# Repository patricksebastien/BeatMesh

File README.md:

# BeatMesh

A module to synchronize via Ableton Link, MIDI, or CV clock. 

Built with PlatformIO and the ESP-IDF framework (espressif32), BeatMesh acts as a hub to keep your hardware and software locked in time.

## 🚀 Features

- **10x MIDI Out ports**
- **Flexible Routing:** Send raw MIDI to all 10 outputs OR filter to keep only the MIDI clock.
- **CV Integration:** CV clock and reset outputs.
- **Ableton Link:** Synchronize seamlessly over WiFi.
- **Ignore Stop:** Jam-proof mode. Stop messages from Link peers, MIDI in or CV in are refused; only BeatMesh itself can stop the clock.
- **MIDI Metronome:** Clock-synced click on the MIDI outputs (note 72 on beat 1, 64 on beats 2-4, channel 1 or 10).
- **Tuner:** One long open-string note on MIDI channel 1, note on at the downbeat of every bar and retriggered at the next one, for tuning by ear. One button cycles through the six guitar strings (E2 A2 D3 G3 B3 E4).
- **Random MIDI (debug mode):** Random pentatonic notes on channels 1-6, random-walk CCs, and a simple four-on-the-floor drum pattern on channel 10, all locked to the clock.
- **OTA Firmware Updates:** Upload new firmware (`.bin`) directly from the web portal, no cable needed.
- **Easy Soldering:** All through-hole components (except USB-C, see below*), beginner-friendly assembly.
- **Easy to Print:** Two-piece 3D-printed case (top and bottom STL), no supports needed, held together with M3 screws.

---

## 🎛️ Custom PCB (KiCad)

The repository includes a production-ready printed circuit board designed in **KiCad 10**. You can find the source files (`.kicad_sch` and `.kicad_pcb`) in the `board/` directory.

<!-- V1 PCB errata (fixed on V2 boards):
> ⚠️ **V1 PCB Errata:** The 2-pin power connector near the USB-C port has its silkscreen polarity printed incorrectly. The actual pinout is **GND, VCC** (not VCC, GND as silkscreened). Wire accordingly to avoid damage.
-->

### Power & USB-C Assembly Notes*

The board only draws 5V power from USB-C; no data lines are used. Two shortcuts make assembly easier:

- **\*Skip the USB-C connector if you are new to soldering.** It is the only surface-mount part on the board; its pins are fine-pitch and tricky to solder by hand. Instead, cut an old USB cable, and solder its **VCC (red)** and **GND (black)** wires directly to the 2-pin power connector pads next to the USB-C footprint. Mind the polarity marked on the silkscreen.
- **The 5.1kΩ resistors (R2, R3) are only needed for USB-C to USB-C.** They are the CC pull-downs that tell a USB-C power adapter or USB-C host to turn on 5V. If you power the board with a **USB-A to USB-C** cable (phone charger, computer port, power bank), 5V is always present on VBUS and R2/R3 can be left unpopulated. In that case only the **VBUS and GND** pins of the USB-C connector need to be soldered.

### Hardware Design Highlights:
- **Form Factor:** 100mm x 100mm, 2-layer board (optimized for low-cost fabrication).
- **MIDI Input:** Fully opto-isolated using a **6N138** optocoupler. The circuit is properly level-shifted to send safe 3.3V logic to the ESP32, while powering the optocoupler with 5V for fast, reliable data transmission.
- **10x MIDI Outputs:** Buffered (using 2N3904 NPN transistors) and split to drive up to 10 distinct devices simultaneously without signal degradation. Designed with space-saving 3.5mm TRS jacks (SJ1-3515N).
- **CV / Sync Out:** Capable of sending analog clock, reset, and play/stop signals to Eurorack/modular gear. Includes **BAT41** Schottky diodes for signal protection.
- **CYD Integration:** Designed to interface cleanly with the Cheap Yellow Display (ESP32-2432S028R) ecosystem via standard 2.54mm pin headers.
- **Power Delivery:** Robust decoupling with 100nF ceramics and 47µF (25V) electrolytics to keep clock and CV paths stable and noise-free.

---

## 🖨️ 3D Printed Case

The case is two pieces, in the `3dprint/` folder:

- `3dprint/BeatMeshV2 - TOP.stl`
- `3dprint/BeatMeshV2 - BOTTOM.stl`

Both print flat on the bed with no supports. Any PLA or PETG works.

Hardware:

- **4x M3 x 30 mm** screws: hold the top and bottom pieces together, screwing straight through both boards.
- **4x M3 x 12 mm** screws with nuts: mount the CYD to the top piece.

---

## 🔊 Optional Metronome (Speaker)

The firmware has a built-in metronome (1200 Hz click on beat 1, 800 Hz on beats 2-4) that plays through the CYD's onboard audio amplifier on GPIO 26. It is **disabled by default** because most builds have no speaker, and the METRONOME button is hidden from the TFT and the web UI.

To use it:

1. Wire the CYD speaker connector to the **SPEAKER IN** header on the BeatMesh board.
2. Connect a small speaker (8 Ω, 0.5-1 W) to the **SPEAKER OUT** header on the BeatMesh board.
3. In `src/main.cpp`, change `#define BEATMESH_METRONOME 0` to `1`.
4. Recompile and flash (`pio run -t upload`, or upload the new `.bin` from the web portal). The metronome code is compiled out, so a rebuild is required; toggling it is not a runtime setting.

The METRONOME button then appears on the main screen (row 2, left of PPQN) and on the web page.

---

## 💻 Installation & Dependencies

> Built with PlatformIO platform `espressif32@6.12.0`, framework `espidf` (ESP-IDF v5.5.0).

External components live under `components/` as git submodules pinned to the versions used in this project:

| Submodule | Upstream | Pinned at |
|---|---|---|
| `components/asio/asio` | [chriskohlhoff/asio](https://github.com/chriskohlhoff/asio) | `asio-1-32-0` |
| `components/esp_abl_link` | [docwilco/esp_abl_link](https://github.com/docwilco/esp_abl_link) | `v3.1.5-1` |
| `components/esp_abl_link/vendor/ableton-link` | [Ableton/link](https://github.com/Ableton/link) | `Link-3.1.5` |
| `components/LovyanGFX` | [lovyan03/LovyanGFX](https://github.com/lovyan03/LovyanGFX) | `1.2.19` |

### Cloning

```bash
git clone --recurse-submodules https://github.com/patricksebastien/BeatMesh.git
```

If you already cloned without `--recurse-submodules`:

```bash
git submodule update --init --recursive
```

> Use `git config --global url."https://github.com/".insteadOf git@github.com:` if you don't have ssh key configured.

### ASIO Patch (Required)
To prevent the ESP32 from rebooting during transient network errors (e.g., `send_to ENOMEM`), ASIO needs a small patch. Link recovers from packet loss gracefully, so we do not want `std::terminate` to abort the program.

Apply the patch shipped in this repo:

```bash
git -C components/asio/asio apply ../../../patches/asio-esp32-rethrow-fix.patch
```

---

## ⚙️ Configuration Files

### 1. `platformio.ini`
Add the following to your environment configuration to ensure correct serial speeds, flash sizing, the OTA partition table, and ASIO compatibility:

```ini
[env:esp32dev]
platform = espressif32@6.12.0
board = esp32dev
framework = espidf
monitor_speed = 115200
board_upload.flash_size = 4MB
board_build.partitions = ota_4mb.csv    ; two ~1.94MB OTA slots (web firmware update)

extra_scripts = pre:git_version.py      ; injects GIT_VERSION (short commit hash) into the build

build_flags =
    -fexceptions
    -D ASIO_STANDALONE
    -D ASIO_NO_TYPEID
```

### 2. `ota_4mb.csv` (Partition Table)
Create this file in the root directory. Link and LovyanGFX make the binary quite large, so the default partition table is too small. Two ~1.94 MB app slots give room for the OTA web update while still fitting the ~1.4 MB image.

```csv
# Name,   Type, SubType, Offset,   Size, Flags
nvs,      data, nvs,     0x9000,   0x4000,
otadata,  data, ota,     0xd000,   0x2000,
phy_init, data, phy,     0xf000,   0x1000,
ota_0,    app,  ota_0,   0x10000,  0x1F0000,
ota_1,    app,  ota_1,   0x200000, 0x1F0000,
```

Changing the partition table requires one flash over USB; OTA works from then on.

### 3. `sdkconfig.defaults`
Create this file in the root directory. The essential settings are below; the full file in the repo also tunes WiFi buffers, LWIP, UDP mailboxes and TCP timeouts for up to 10 Link peers plus the web portal.

```ini
# Flash Size & Speed (CYD has a 4MB Flash chip)
CONFIG_ESPTOOLPY_FLASHSIZE_4MB=y
CONFIG_ESPTOOLPY_FLASHFREQ_80M=y
CONFIG_ESPTOOLPY_FLASHMODE_QIO=y

# C++ Exceptions (Required for ASIO/Link)
CONFIG_COMPILER_CXX_EXCEPTIONS=y
CONFIG_COMPILER_CXX_RTTI=y

# Partition Table Layout (OTA, see ota_4mb.csv above)
CONFIG_PARTITION_TABLE_CUSTOM=y
CONFIG_PARTITION_TABLE_CUSTOM_FILENAME="ota_4mb.csv"
CONFIG_BOOTLOADER_APP_ROLLBACK_ENABLE=y

# CPU Frequency (Ensure Link timing on Core 1 and Display/WiFi on Core 0 run smoothly)
CONFIG_ESP_DEFAULT_CPU_FREQ_MHZ_240=y
CONFIG_ESP_DEFAULT_CPU_FREQ_MHZ=240

# Link tasks on Core 1 (WiFi stays on Core 0)
CONFIG_LINK_ESP_TASK_CORE_ID=1

# LWIP (Networking for Link - Multicast support is crucial)
CONFIG_LWIP_MAX_SOCKETS=32
CONFIG_LWIP_IGMP=y
CONFIG_LWIP_SO_REUSE=y

# Disable Bluetooth (WiFi only)
CONFIG_BT_ENABLED=n
```

### 4. `src/CMakeLists.txt`
Include the necessary libraries via `REQUIRES` so ESP-IDF links them properly:

```cmake
idf_component_register(SRCS "main.cpp"
                    INCLUDE_DIRS "."
                    REQUIRES LovyanGFX esp_http_server nvs_flash esp_wifi esp_event esp_abl_link app_update)
```

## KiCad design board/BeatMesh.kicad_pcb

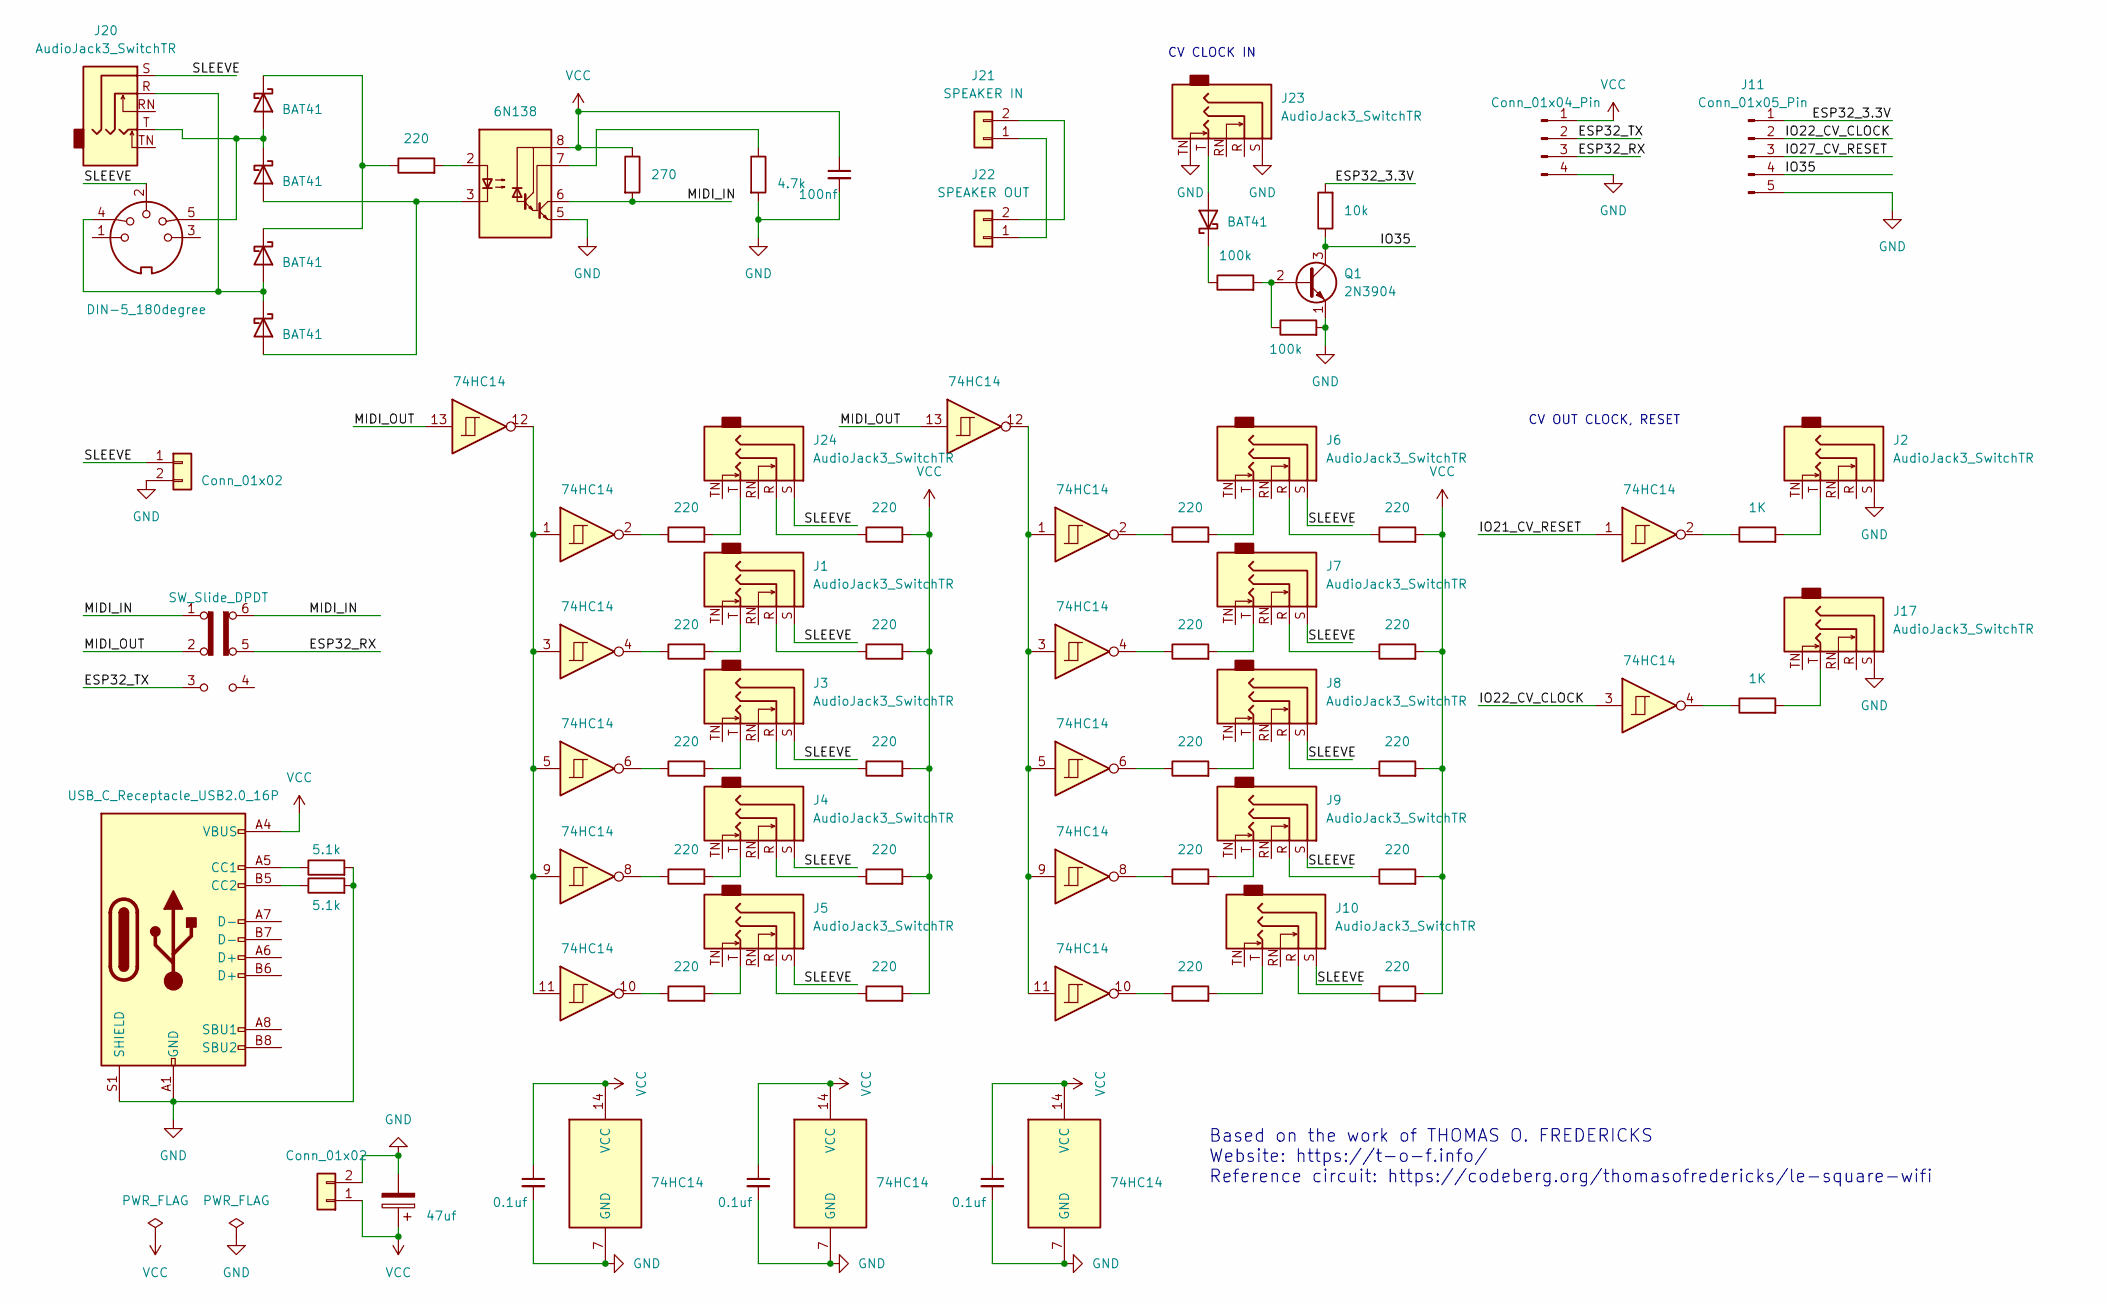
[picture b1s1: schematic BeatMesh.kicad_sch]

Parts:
C1, C2, C6: 0.1uf; C_Disc_D5.0mm_W2.5mm_P5.00mm
C3: 100nf; C_Disc_D5.0mm_W2.5mm_P5.00mm
C4: 47uf; CP_Radial_D5.0mm_P2.00mm
D1, D2, D3, D4, D6: BAT41; D_DO-35_SOD27_P7.62mm_Horizontal
J1, J2, J3, J4, J5, J6, J7, J8, J9, J10, J17, J20, J23, J24: AudioJack3_SwitchTR; Jack_3.5mm_CUI_SJ1-3515N_Horizontal
J11: Conn_01x05_Pin; PinHeader_1x05_P2.54mm_Vertical
J12: DIN-5_180degree; CUI_SDS-50J
J13: USB_C_Receptacle_USB2.0_16P; USB_C_Receptacle_HRO_TYPE-C-31-M-12
J14: Conn_01x04_Pin; PinHeader_1x04_P2.54mm_Vertical
J15, J16: Conn_01x02; PinHeader_1x02_P2.54mm_Vertical
J21: SPEAKER IN; PinHeader_1x02_P2.54mm_Vertical
J22: SPEAKER OUT; PinHeader_1x02_P2.54mm_Vertical
Q1: 2N3904; TO-92_Inline_Wide
R1, R6, R7, R8, R9, R10, R11, R12, R13, R14, R15, R16, R17, R18, R19, R20, R21, R22, R23, R24, R25: 220; R_Axial_DIN0204_L3.6mm_D1.6mm_P5.08mm_Horizontal
R2, R3: 5.1k; R_Axial_DIN0204_L3.6mm_D1.6mm_P5.08mm_Horizontal
R4: 270; R_Axial_DIN0204_L3.6mm_D1.6mm_P5.08mm_Horizontal
R5: 4.7k; R_Axial_DIN0204_L3.6mm_D1.6mm_P5.08mm_Horizontal
R26, R28: 1K; R_Axial_DIN0204_L3.6mm_D1.6mm_P5.08mm_Horizontal
R29, R31: 100k; R_Axial_DIN0204_L3.6mm_D1.6mm_P5.08mm_Horizontal
R30: 10k; R_Axial_DIN0204_L3.6mm_D1.6mm_P5.08mm_Horizontal
SW1: SW_Slide_DPDT; SW_E-Switch_EG2219_DPDT_Angled
U1, U2, U4: 74HC14; DIP-14_W7.62mm
U3: 6N138; DIP-8_W7.62mm

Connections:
/ESP32_3.3V: J11.1, R30.2
/ESP32_RX: J14.3, SW1.5 (B)
/ESP32_TX: J14.2, SW1.3 (C)
/IO21_CV_RESET: U4.1
/IO22_CV_CLOCK: J11.2, U4.3
/IO27_CV_RESET: J11.3
/IO35: J11.4, Q1.3 (C), R30.1
/MIDI_IN: R4.2, SW1.1 (A), SW1.6 (C), U3.6 (VO2)
/MIDI_OUT: SW1.2 (B), U1.13, U2.13
/SLEEVE: J1.S, J3.S, J4.S, J5.S, J6.S, J7.S, J8.S, J9.S, J10.S, J12.2, J15.1, J20.S, J24.S
GND: C1.2, C2.2, C3.2, C4.2, C6.2, J2.S, J11.5, J13.A1 (GND), J13.A12 (GND), J13.B1 (GND), J13.B12 (GND), J13.S1 (SHIELD), J14.4, J15.2, J16.2, J17.S, J23.S, J23.TN, Q1.1 (E), R2.2, R3.2, R5.2, R31.2, U1.7 (GND), U2.7 (GND), U3.5 (GND), U4.7 (GND)
unnamed: D1.2 (A), D2.1 (K), J12.5, J20.T
unnamed: D1.1 (K), D3.1 (K), R1.1
unnamed: D2.2 (A), D4.2 (A), U3.3 (C2)
unnamed: D3.2 (A), D4.1 (K), J12.4, J20.R
unnamed: D6.2 (A), J23.T
unnamed: D6.1 (K), R29.1
unnamed: J1.R, R12.1
unnamed: J1.T, R7.2
unnamed: J2.T, R26.2
unnamed: J3.R, R13.1
unnamed: J3.T, R8.2
unnamed: J4.R, R14.1
unnamed: J4.T, R9.2
unnamed: J5.R, R15.1
unnamed: J5.T, R10.2
unnamed: J6.R, R21.1
unnamed: J6.T, R16.2
unnamed: J7.R, R22.1
unnamed: J7.T, R17.2
unnamed: J8.R, R23.1
unnamed: J8.T, R18.2
unnamed: J9.R, R24.1
unnamed: J9.T, R19.2
unnamed: J10.R, R25.1
unnamed: J10.T, R20.2
unnamed: J13.A5 (CC1), R2.1
unnamed: J13.B5 (CC2), R3.1
unnamed: J17.T, R28.2
unnamed: J21.1, J22.1
unnamed: J21.2, J22.2
unnamed: J24.R, R11.1
unnamed: J24.T, R6.2
unnamed: Q1.2 (B), R29.2, R31.1
unnamed: R6.1, U2.2
unnamed: R7.1, U2.4
unnamed: R8.1, U2.6
unnamed: R9.1, U2.8
unnamed: R10.1, U2.10
unnamed: R16.1, U1.2
unnamed: R17.1, U1.4
unnamed: R18.1, U1.6
unnamed: R19.1, U1.8
unnamed: R20.1, U1.10
unnamed: R26.1, U4.2
unnamed: R28.1, U4.4
unnamed: U1.1, U1.3, U1.5, U1.9, U1.11, U1.12
unnamed: U2.1, U2.3, U2.5, U2.9, U2.11, U2.12
unnamed: R1.2, U3.2 (C1)
unnamed: R5.1, U3.7 (VO1)
VCC: C1.1, C2.1, C3.1, C4.1, C6.1, J13.A4 (VBUS), J13.A9 (VBUS), J13.B4 (VBUS), J13.B9 (VBUS), J14.1, J16.1, R4.1, R11.2, R12.2, R13.2, R14.2, R15.2, R21.2, R22.2, R23.2, R24.2, R25.2, U1.14 (VCC), U2.14 (VCC), U3.8 (VCC), U4.14 (VCC)

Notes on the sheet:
Based on the work of THOMAS O. FREDERICKS Website: https://t-o-f.info/ Reference circuit: https://codeberg.org/thomasofredericks/le-square-wifi
CV CLOCK IN
CV OUT CLOCK, RESET

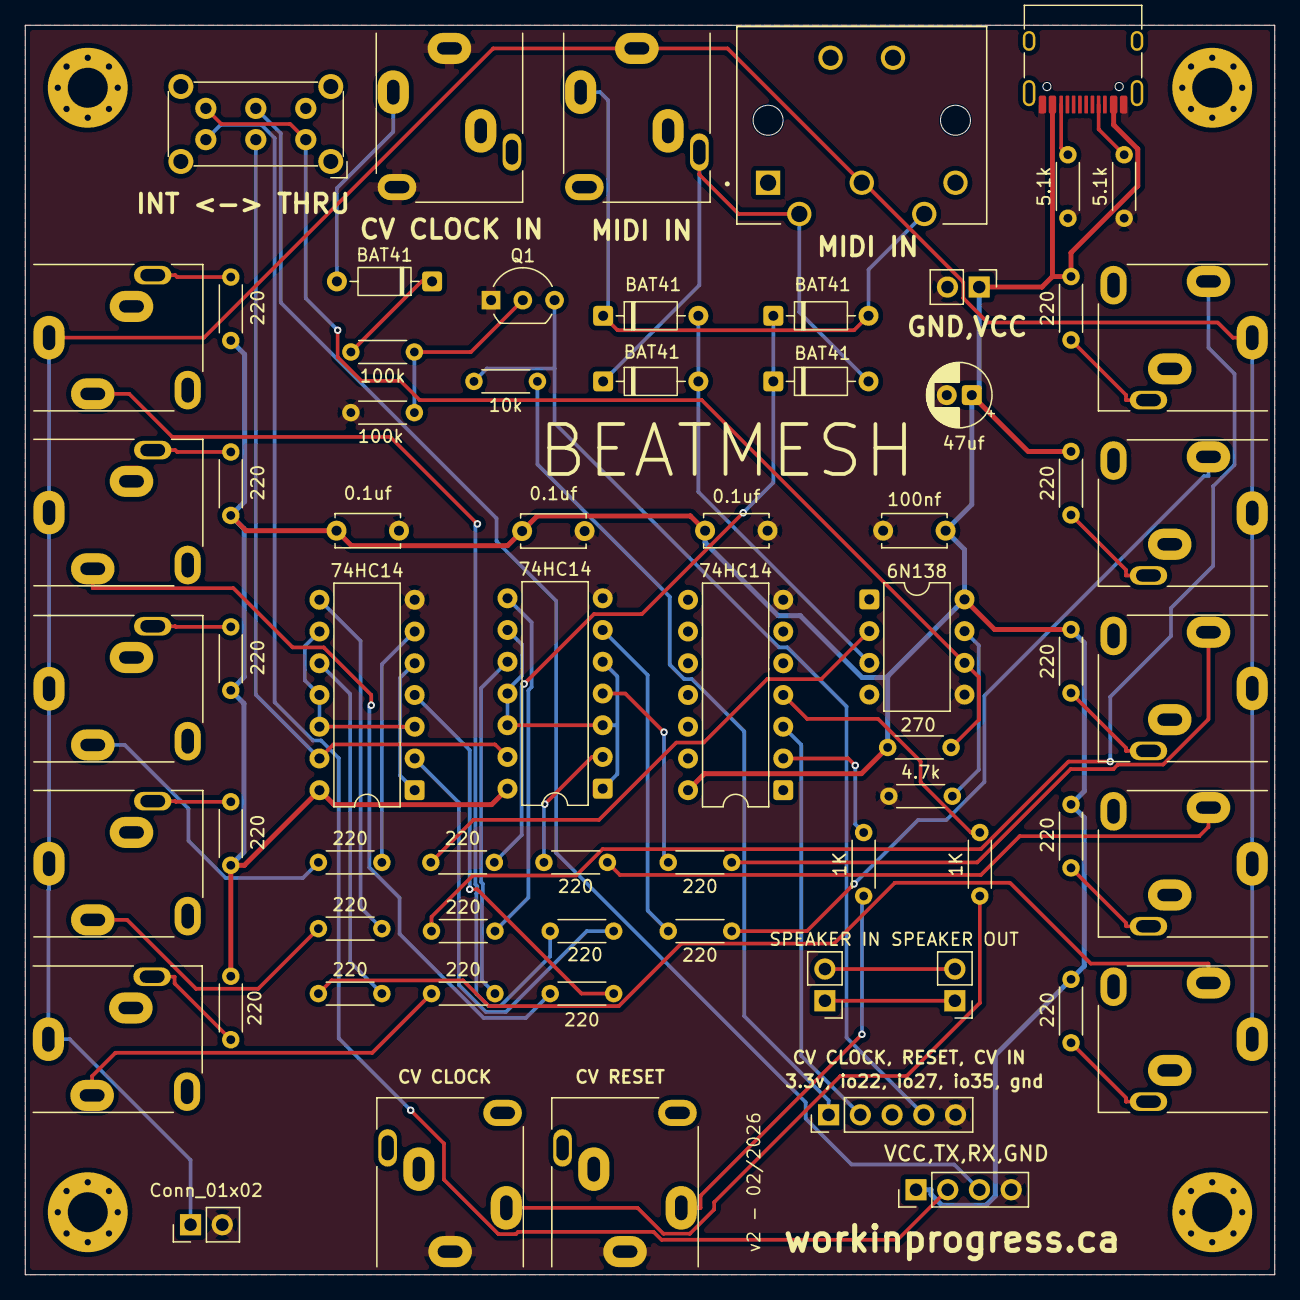
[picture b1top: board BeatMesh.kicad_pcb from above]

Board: 2 copper layers, 100.0 x 100.0 mm, 72 parts (0 on the bottom side), 59 nets.

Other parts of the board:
REF1, REF2, REF3, REF4: MountingHole_3.2mm_M3_Pad_Via

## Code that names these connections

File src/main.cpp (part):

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static uint8_t g_mon_data_needed = 0;

// --- MIDI Clock (UART2 routed to CYD's UART0 header pins via GPIO matrix) ---
// Board net ESP32_TX = GPIO 1 (U0TXD), ESP32_RX = GPIO 3 (U0RXD).
// Using UART_NUM_2 on these pins avoids touching the boot-ROM UART0 driver,
// but the GPIO mux will steal GPIO1/3 from UART0 — USB serial console stops
// working once midi_init() runs. Disconnect/close the USB serial monitor when
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#if BEATMESH_METRONOME
    metronome_init();
#endif // BEATMESH_METRONOME
    xTaskCreatePinnedToCore(midi_clock_task, "midi_out", 4096, &g_link_state, 10, NULL, 1);
    xTaskCreatePinnedToCore(midi_in_task, "midi_in", 4096, &g_link_state, 10, NULL, 1);

    wifi_config_t sta_cfg;
    esp_wifi_get_config(WIFI_IF_STA, &sta_cfg);
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
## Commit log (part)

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2026-05-03 adding CV, metronome, PPQN
2026-05-03 adding midi monitoring
2026-05-04 adjusting the doc
2026-05-05 using submodule - doc adjusted
2026-05-05 using submodule - pin idf - adjusted installation doc
2026-05-05 restore asio
2026-05-05 config global
2026-05-07 errata V1 + updated to kicad 10
2026-05-07 kicad 10
2026-06-06 modulo for ppqn, added TODO in pcb
2026-06-11 notes on pins
2026-06-16 board v2
